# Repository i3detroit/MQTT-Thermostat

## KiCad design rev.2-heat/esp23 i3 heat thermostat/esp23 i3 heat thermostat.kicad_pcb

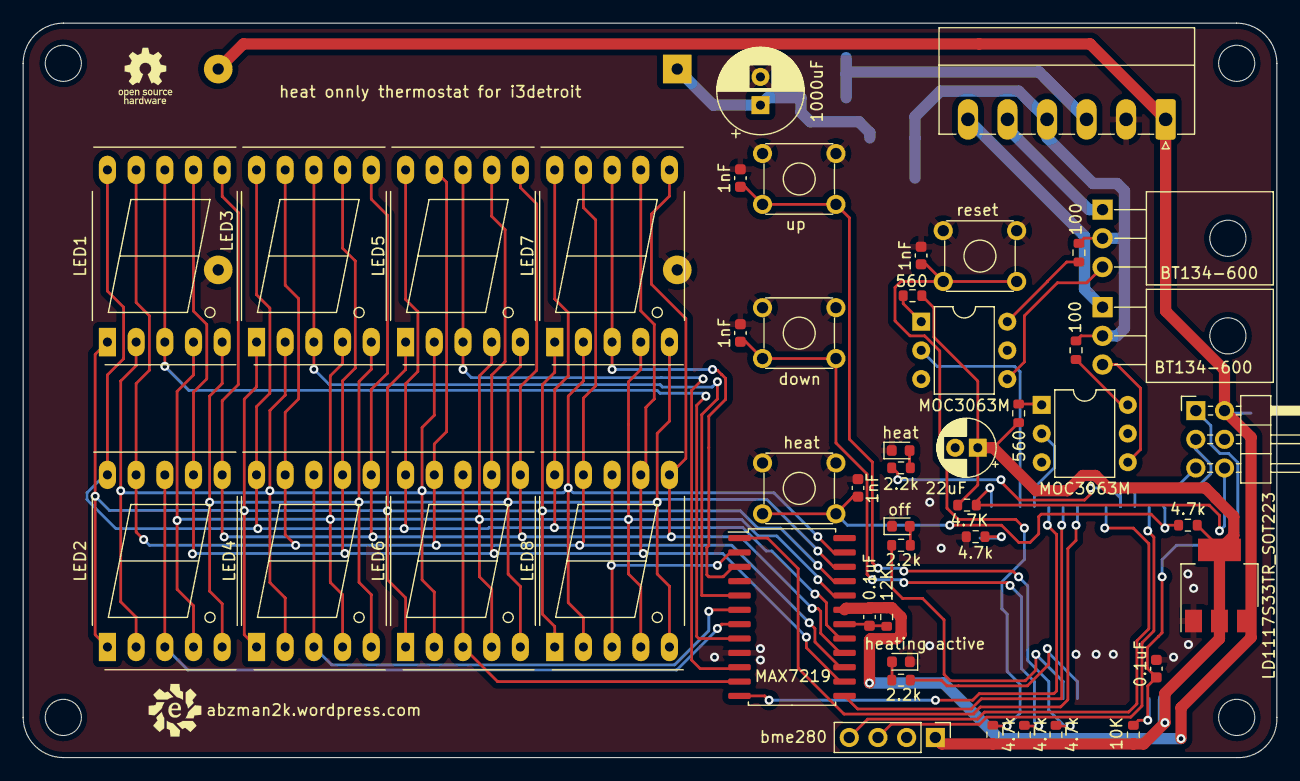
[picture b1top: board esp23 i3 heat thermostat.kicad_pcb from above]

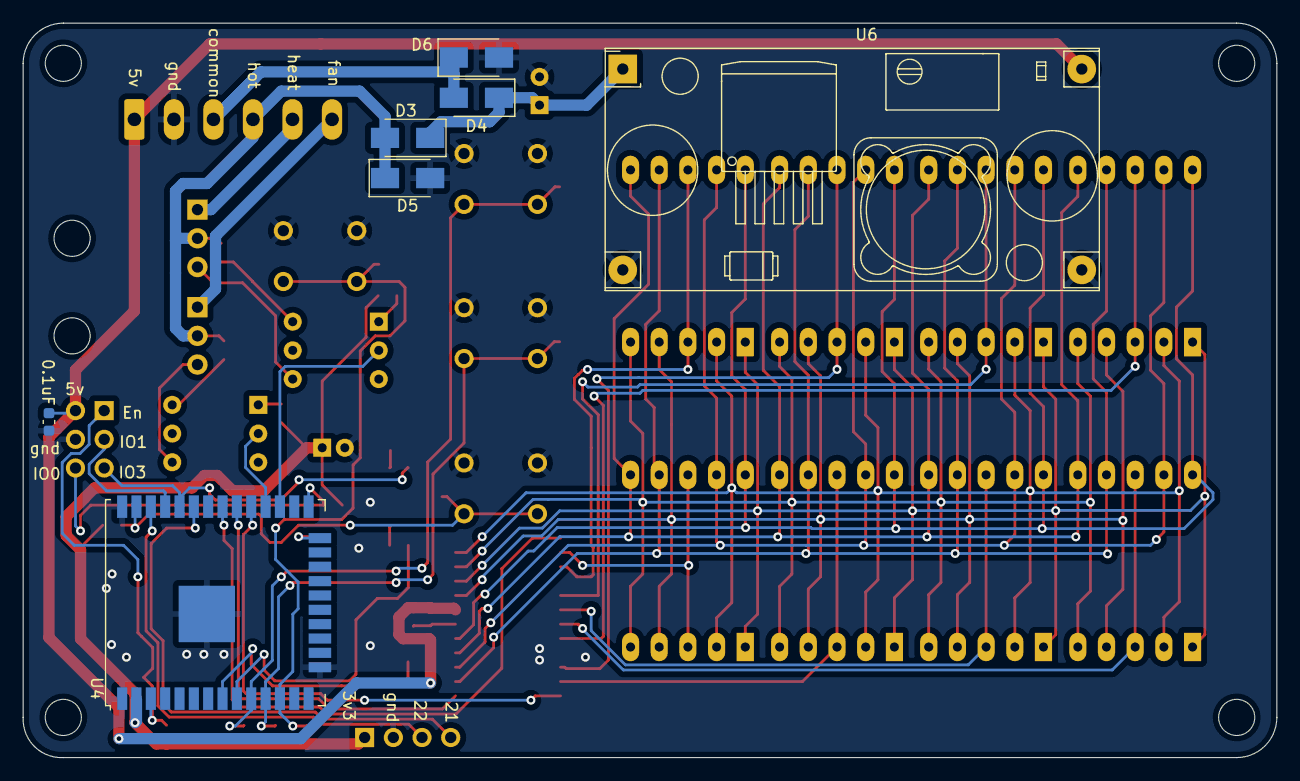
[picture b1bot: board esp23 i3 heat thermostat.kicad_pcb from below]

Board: 2 copper layers, 111.0 x 65.0 mm, 54 parts (7 on the bottom side), 52 nets.

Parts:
C1, C3, C7: 0.1uF; C_0603_1608Metric
C5: 1000uF; CP_Radial_D7.5mm_P2.50mm
C6: 22uF; CP_Radial_D5.0mm_P2.00mm
C8, C9, C10, C11: 1nF; C_0603_1608Metric
D3, D4, D5, D6: 1N4004; D_SMA
D8, D9, D10: LED; LED_0603_1608Metric
J1: Conn_01x06; PhoenixContact_MC_1,5_6-G-3.5_1x06_P3.50mm_Horizontal
J2: bme280; PinHeader_1x04_P2.54mm_Vertical
J4: Conn_02x03_Odd_Even; PinHeader_2x03_P2.54mm_Horizontal
LED1, LED2, LED3, LED4, LED5, LED6, LED7, LED8: LTS-6980HR; 7SegmentLED_LTS6760_LTS6780
Q1, Q2: BT134-600; TO-126-3_Horizontal_TabDown
R1: 12K; R_0603_1608Metric
R4, R5: 560; R_0603_1608Metric
R6, R7: 100; R_0603_1608Metric
R8, R15, R16, R17, R18: 4.7k; R_0603_1608Metric
R9: 10K; R_0603_1608Metric
R14: 4.7K; R_0603_1608Metric
R19, R20, R21: 2.2k; R_0603_1608Metric
SW2, SW3, SW4, SW5: SW_MEC_5E; SW_TH_Tactile_Omron_B3F-10xx
U1: MAX7219; SOP-24_7.5x15.4mm_P1.27mm
U2, U3: MOC3063M; DIP-6_W7.62mm
U4: ESP32-WROOM-32U
U5: LD1117S33TR_SOT223; SOT-223-3_TabPin2
U6: YAAJ_DCDC_StepDown_LM2596

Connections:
+3V3: C6.1, J2.1, R4.1, R5.1, R9.1, R14.1, R15.1, R16.1, R17.1, R18.1, U4.2 (VDD), U5.2 (VO)
+5V: C1.1, C7.1, J1.1, J4.2, R1.1, U1.19 (V+), U5.3 (VI), U6.4 (Vout)
+24V: C5.1, D3.1 (K), D4.1 (K), U6.1 (Vin)
/A: LED1.7 (a), LED2.7 (a), LED3.7 (a), LED4.7 (a), LED5.7 (a), LED6.7 (a), LED7.7 (a), LED8.7 (a), U1.14 (SEG_A)
/B: LED1.6 (b), LED2.6 (b), LED3.6 (b), LED4.6 (b), LED5.6 (b), LED6.6 (b), LED7.6 (b), LED8.6 (b), U1.16 (SEG_B)
/C: LED1.4 (c), LED2.4 (c), LED3.4 (c), LED4.4 (c), LED5.4 (c), LED6.4 (c), LED7.4 (c), LED8.4 (c), U1.20 (SEG_C)
/D: LED1.2 (d), LED2.2 (d), LED3.2 (d), LED4.2 (d), LED5.2 (d), LED6.2 (d), LED7.2 (d), LED8.2 (d), U1.23 (SEG_D)
/D1: LED8.3 (C.K.), LED8.8 (C.K.), U1.2 (DIG_0)
/D2: LED6.3 (C.K.), LED6.8 (C.K.), U1.11 (DIG_1)
/D3: LED4.3 (C.K.), LED4.8 (C.K.), U1.6 (DIG_2)
/D4: LED2.3 (C.K.), LED2.8 (C.K.), U1.7 (DIG_3)
/D5: LED7.3 (C.K.), LED7.8 (C.K.), U1.3 (DIG_4)
/D6: LED5.3 (C.K.), LED5.8 (C.K.), U1.10 (DIG_5)
/D7: LED3.3 (C.K.), LED3.8 (C.K.), U1.5 (DIG_6)
/D8: LED1.3 (C.K.), LED1.8 (C.K.), U1.8 (DIG_7)
/DP: LED1.5 (DP), LED2.5 (DP), LED3.5 (DP), LED4.5 (DP), LED5.5 (DP), LED6.5 (DP), LED7.5 (DP), LED8.5 (DP), U1.22 (SEG_DP)
/E: LED1.1 (e), LED2.1 (e), LED3.1 (e), LED4.1 (e), LED5.1 (e), LED6.1 (e), LED7.1 (e), LED8.1 (e), U1.21 (SEG_E)
/ESP_EN: C3.1, J4.1, R9.2, U4.3 (EN)
/ESP_IO0: J4.6, R14.2, U4.25 (IO0)
/ESP_IO1: J4.3, U4.35 (TXD0/IO1)
/ESP_IO2: R8.1, U4.24 (IO2)
/ESP_IO3: J4.5, R20.1, U4.34 (RXD0/IO3)
/ESP_IO5: U1.12 (LOAD), U4.29 (IO5)
/ESP_IO16: U2.2, U4.27 (IO16)
/ESP_IO17: U3.2, U4.28 (IO17)
/ESP_IO18: U1.13 (CLK), U4.30 (IO18)
/ESP_IO19: U1.1 (DIN), U4.31 (IO19)
/ESP_IO21: J2.4, U4.33 (IO21)
/ESP_IO22: J2.3, U4.36 (IO22)
/ESP_IO23: C11.2, R18.2, SW5.3 (K), SW5.4 (A), U4.37 (IO23)
/ESP_IO25: C10.2, R17.2, SW4.3 (K), SW4.4 (A), U4.10 (IO25)
/ESP_IO26: C9.2, R16.2, SW3.3 (K), SW3.4 (A), U4.11 (IO26)
/ESP_IO27: C8.2, R15.2, SW2.3 (K), SW2.4 (A), U4.12 (IO27)
/ESP_IO32: R19.1, U4.8 (IO32)
/ESP_IO33: R21.1, U4.9 (IO33)
/F: LED1.9 (f), LED2.9 (f), LED3.9 (f), LED4.9 (f), LED5.9 (f), LED6.9 (f), LED7.9 (f), LED8.9 (f), U1.15 (SEG_F)
/Fan: J1.6, Q2.1 (A1)
/G: LED1.10 (g), LED2.10 (g), LED3.10 (g), LED4.10 (g), LED5.10 (g), LED6.10 (g), LED7.10 (g), LED8.10 (g), U1.17 (SEG_G)
/Heat: J1.5, Q1.1 (A1)
/Hot: D3.2 (A), D5.1 (K), J1.4, Q1.2 (A2), Q2.2 (A2), R6.2, R7.2
/common: D4.2 (A), D6.1 (K), J1.3
GND: C3.2, C5.2, C6.2, C7.2, C8.1, C9.1, C10.1, C11.1, D5.2 (A), D6.2 (A), D8.1 (K), D9.1 (K), D10.1 (K), J1.2, J2.2, J4.4, R8.2, SW2.1, SW2.2, SW3.1, SW3.2, SW4.1, SW4.2, SW5.1, SW5.2, U1.4 (GND), U1.9 (GND), U4.1 (GND), U4.15 (GND), U4.38 (GND), U4.39 (GND), U5.1 (GND), U6.2 (GND), U6.3 (GND)
unnamed: C1.2, R1.2, U1.18 (ISET)
unnamed: D8.2 (A), R19.2
unnamed: D9.2 (A), R20.2
unnamed: D10.2 (A), R21.2
unnamed: Q1.3 (G), U2.4
unnamed: Q2.3 (G), U3.4
unnamed: R4.2, U2.1
unnamed: R5.2, U3.1
unnamed: R6.1, U2.6
unnamed: R7.1, U3.6

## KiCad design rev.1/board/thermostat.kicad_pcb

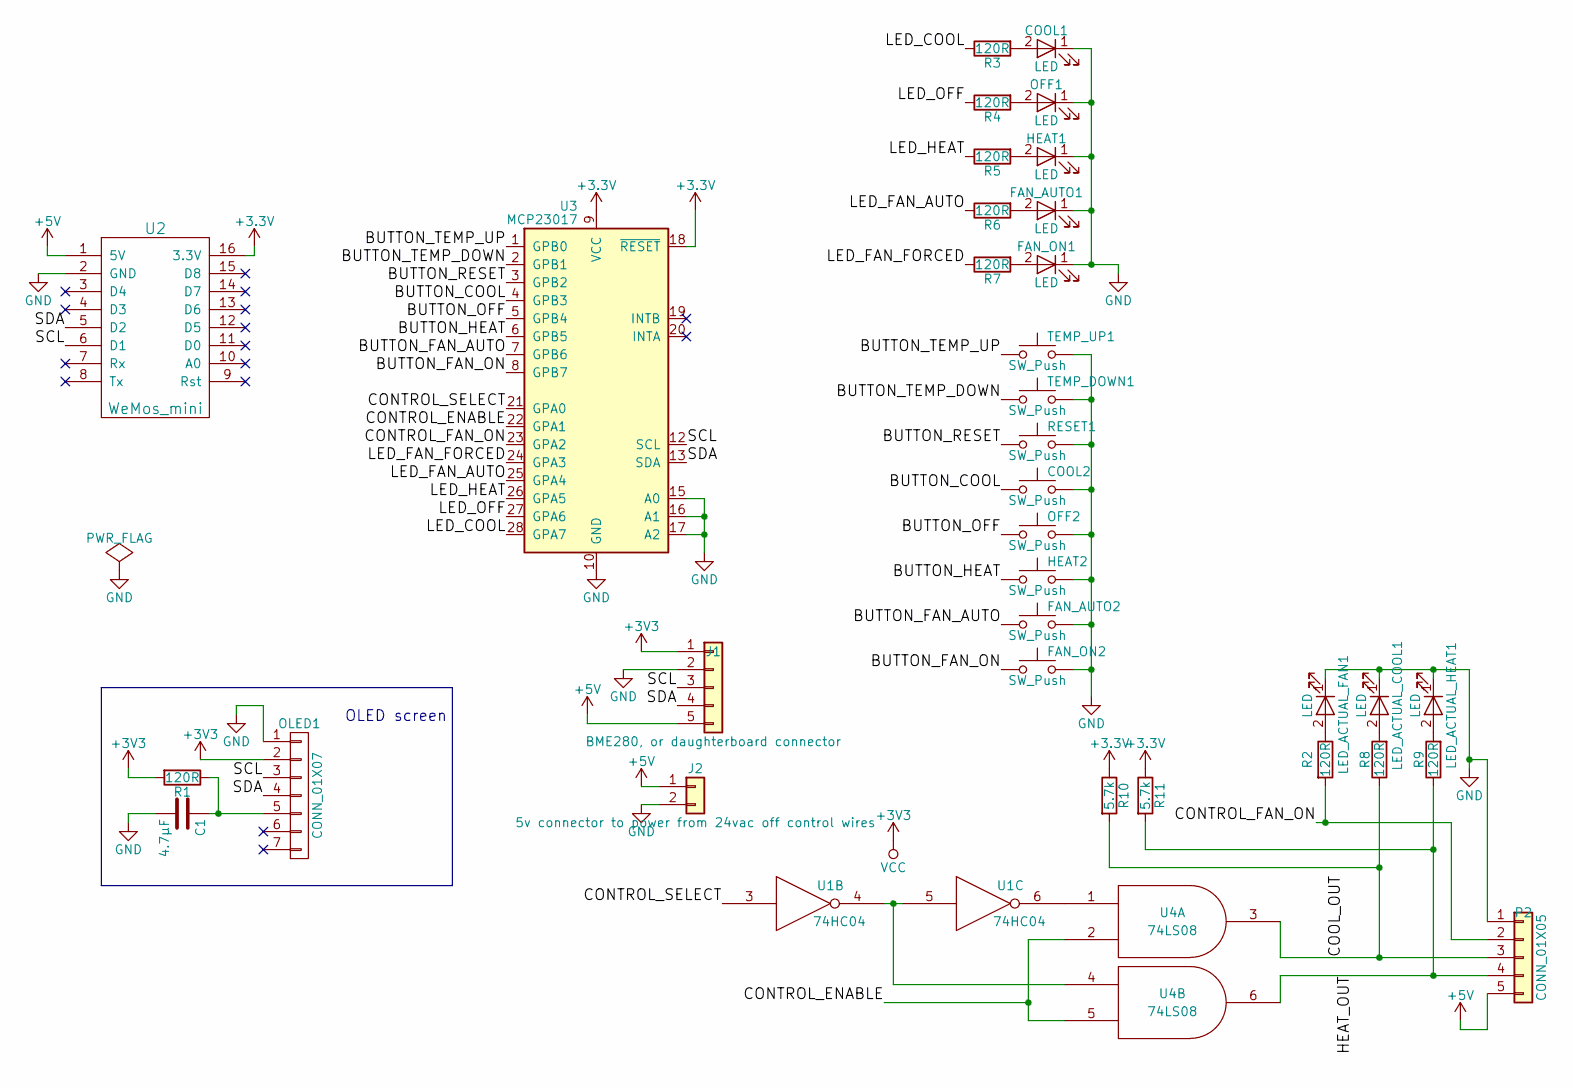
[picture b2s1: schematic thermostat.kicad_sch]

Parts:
C1: 4.7µF; C_0603_HandSoldering
COOL1: LED; LED_D3.0mm
COOL2: SW_Push; SW_Tactile_SPST_Angled
FAN_AUTO1: LED; LED_D3.0mm
FAN_AUTO2: SW_Push; SW_PUSH_6mm
FAN_ON1: LED; LED_D3.0mm
FAN_ON2: SW_Push; SW_PUSH_6mm
HEAT1: LED; LED_D3.0mm
HEAT2: SW_Push; SW_Tactile_SPST_Angled
J1: BME280, or daughterboard connector; Pin_Header_Straight_1x05
J2: 5v connector to power from 24vac off control wires; Pin_Header_Straight_1x02
LED_ACTUAL_COOL1: LED; LED_D3.0mm
LED_ACTUAL_FAN1: LED; LED_D3.0mm
LED_ACTUAL_HEAT1: LED; LED_D3.0mm
OFF1: LED; LED_D3.0mm
OFF2: SW_Push; SW_Tactile_SPST_Angled
OLED1: CONN_01X07; OLED_I2C_SPI
P2: CONN_01X05; Pin_Header_Straight_1x05
R1, R2, R3, R4, R5, R6, R7, R8, R9: 120R; R_0603_HandSoldering
R10, R11: 5.7k; R_0603_HandSoldering
RESET1: SW_Push; SW_PUSH_6mm
TEMP_DOWN1: SW_Push; SW_PUSH_6mm
TEMP_UP1: SW_Push; SW_PUSH_6mm
U1: 74HC04; DIP-14_W7.62mm
U2: WeMos_mini; D1_mini_board
U3: MCP23017; DIP-28_W7.62mm
U4: 74LS08; DIP-14_W7.62mm_cuttable-trace

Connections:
+5V: J1.5, J2.1, P2.5, U2.1 (5V)
/BUTTON_COOL: COOL2.1, U3.4 (GPB3)
/BUTTON_FAN_AUTO: FAN_AUTO2.1, U3.7 (GPB6)
/BUTTON_FAN_ON: FAN_ON2.1, U3.8 (GPB7)
/BUTTON_HEAT: HEAT2.1, U3.6 (GPB5)
/BUTTON_OFF: OFF2.1, U3.5 (GPB4)
/BUTTON_RESET: RESET1.1, U3.3 (GPB2)
/BUTTON_TEMP_DOWN: TEMP_DOWN1.1, U3.2 (GPB1)
/BUTTON_TEMP_UP: TEMP_UP1.1, U3.1 (GPB0)
/CONTROL_ENABLE: U3.22 (GPA1), U4.2, U4.5
/CONTROL_FAN_ON: P2.2, R2.2, U3.23 (GPA2)
/CONTROL_SELECT: U1.3, U3.21 (GPA0)
/COOL_OUT: P2.3, R8.1, R10.2, U4.3
/HEAT_OUT: P2.4, R9.1, R11.2, U4.6
/LED_COOL: R3.1, U3.28 (GPA7)
/LED_FAN_AUTO: R6.1, U3.25 (GPA4)
/LED_FAN_FORCED: R7.1, U3.24 (GPA3)
/LED_HEAT: R5.1, U3.26 (GPA5)
/LED_OFF: R4.1, U3.27 (GPA6)
/SCL: J1.3, OLED1.3, U2.6 (D1), U3.12 (SCL)
/SDA: J1.4, OLED1.4, U2.5 (D2), U3.13 (SDA)
GND: C1.2, COOL1.1 (K), COOL2.2, FAN_AUTO1.1 (K), FAN_AUTO2.2, FAN_ON1.1 (K), FAN_ON2.2, HEAT1.1 (K), HEAT2.2, J1.2, J2.2, LED_ACTUAL_COOL1.1 (K), LED_ACTUAL_FAN1.1 (K), LED_ACTUAL_HEAT1.1 (K), OFF1.1 (K), OFF2.2, OLED1.1, P2.1, RESET1.2, TEMP_DOWN1.2, TEMP_UP1.2, U1.7 (GND), U2.2 (GND), U3.10 (GND), U3.15 (A0), U3.16 (A1), U3.17 (A2), U4.7 (GND)
unnamed: C1.1, OLED1.5, R1.1
unnamed: COOL1.2 (A), R3.2
unnamed: FAN_AUTO1.2 (A), R6.2
unnamed: FAN_ON1.2 (A), R7.2
unnamed: HEAT1.2 (A), R5.2
unnamed: LED_ACTUAL_COOL1.2 (A), R8.2
unnamed: LED_ACTUAL_FAN1.2 (A), R2.1
unnamed: LED_ACTUAL_HEAT1.2 (A), R9.2
unnamed: OFF1.2 (A), R4.2
unnamed: U1.4, U1.5, U4.4
unnamed: U1.6, U4.1

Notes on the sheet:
OLED screen

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
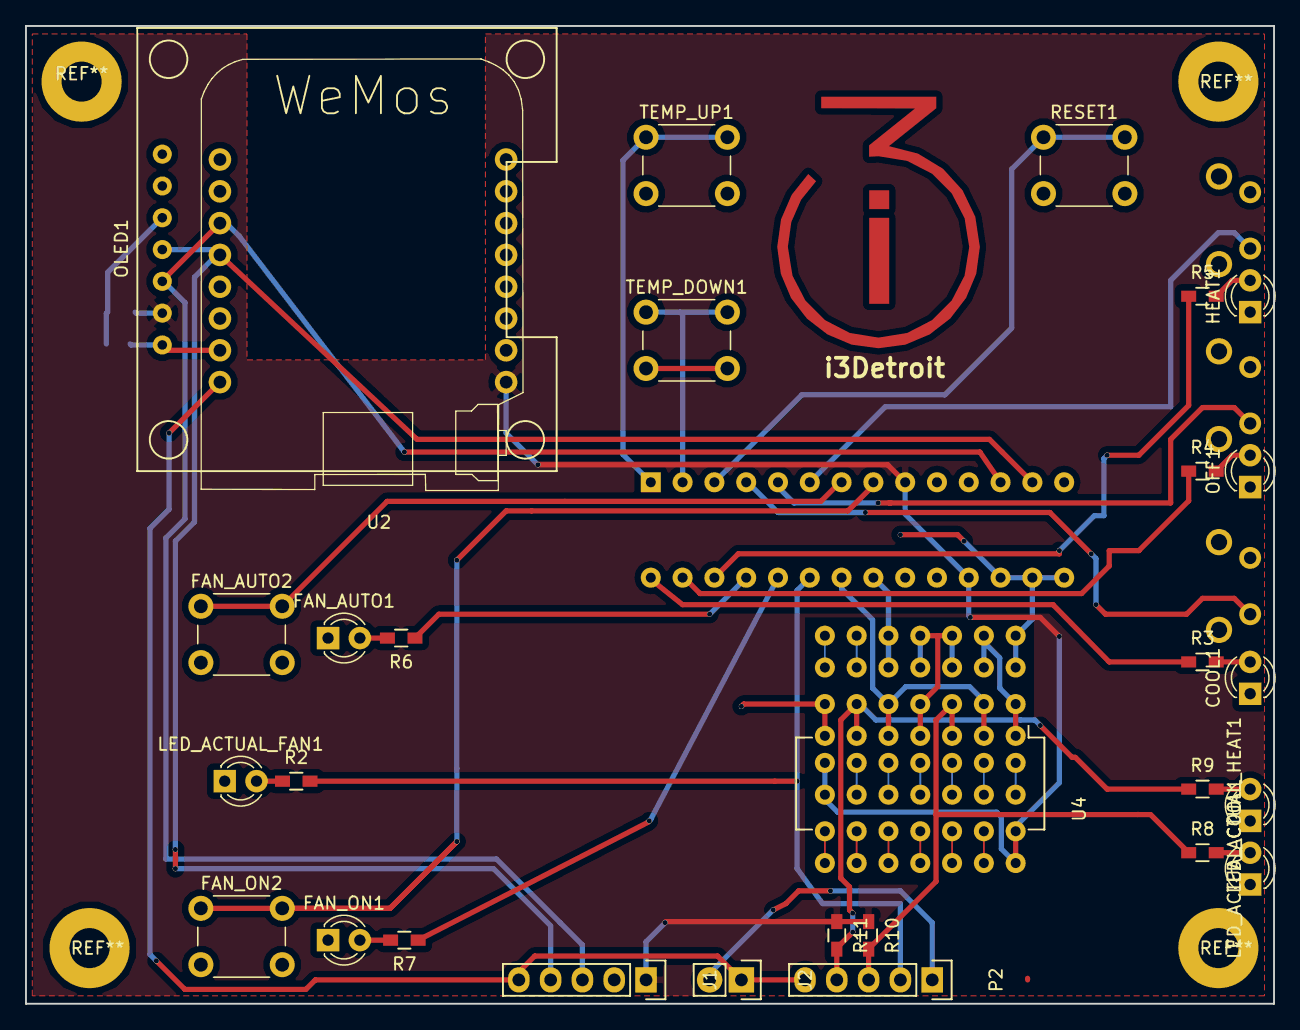
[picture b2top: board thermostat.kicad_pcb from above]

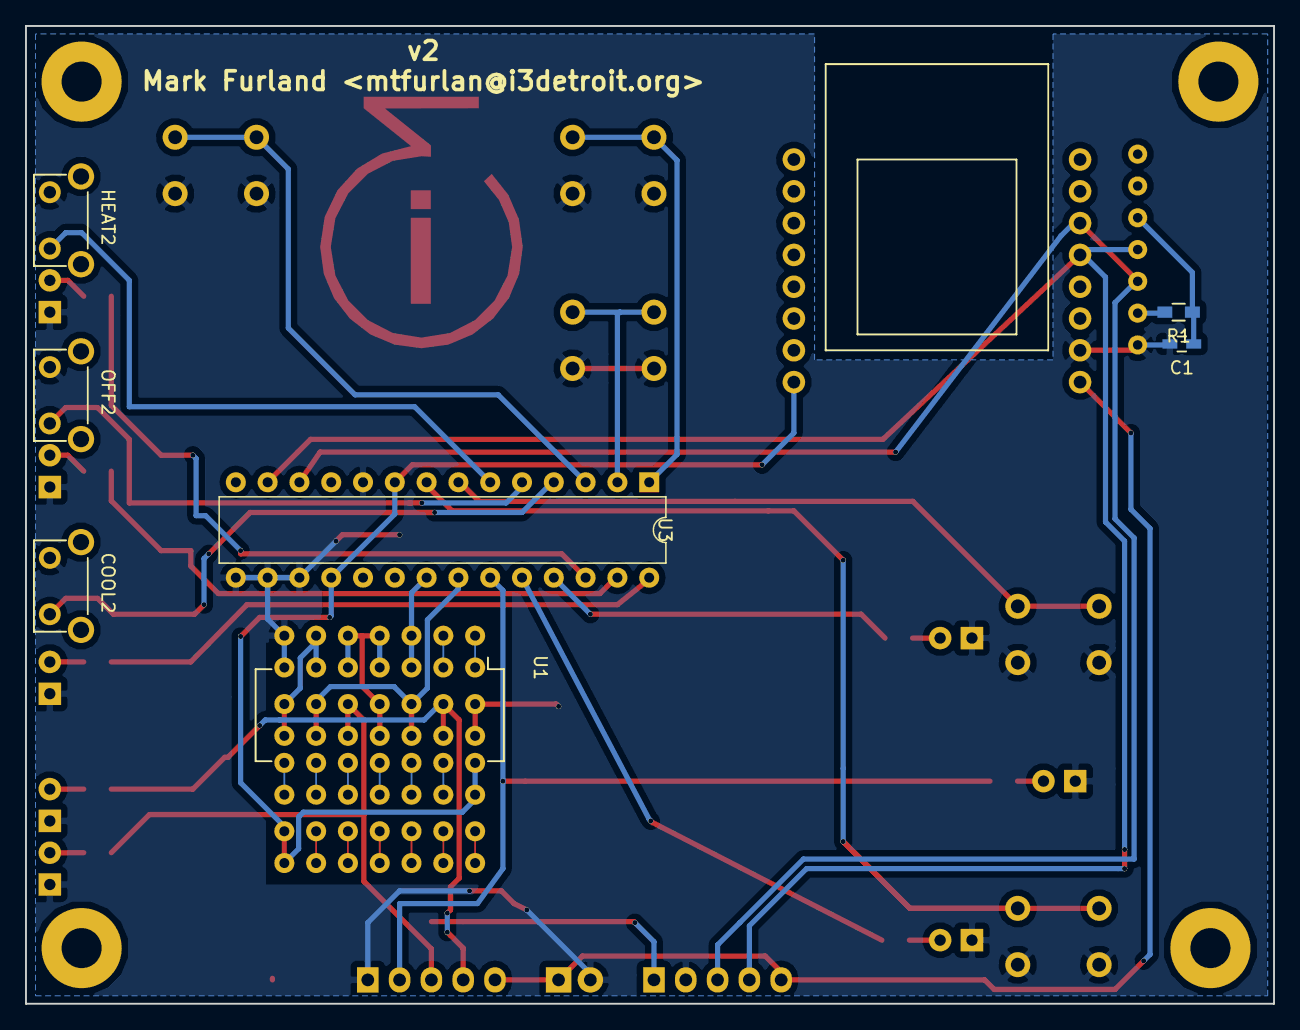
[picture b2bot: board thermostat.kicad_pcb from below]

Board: 2 copper layers, 99.7 x 78.1 mm, 37 parts (7 on the bottom side), 34 nets.

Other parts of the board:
svg2mod: G***; i3Logo

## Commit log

2020-02-15 feat: move to it's own repo
2020-04-10 feat(local.h): add local settings file
2020-08-30 build(makefile): add makefile that can set wifi settings and such
2020-08-30 Make tests less intrusive but also broken
2020-08-30 fix(i3 logo): Magic fix from abzman
    Closes #8
2022-02-15 moved files and added second rev thermostat schematic
2022-02-15 initial layout for UX
2022-02-19 layout attempt 1
2022-02-19 added mounting holes
2022-02-19 add fourth corner hole
2022-03-13 generated gerbers
2022-03-13 Update fp-info-cache
2022-04-01 added test code in arduino to validate some hardware
